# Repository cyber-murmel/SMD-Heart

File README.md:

# SMD Heart
This PCB is supposed the be a pendant for a necklace or similar.
The circuit is a simple 13 stage ring oscillator which makes 13 LEDs fade.
It's powered by a single CR2032 coin cell.

The files are created using KiCAD Version 5.0.0-rc2.
Thus I had to include some footprints and 3D files in this project.

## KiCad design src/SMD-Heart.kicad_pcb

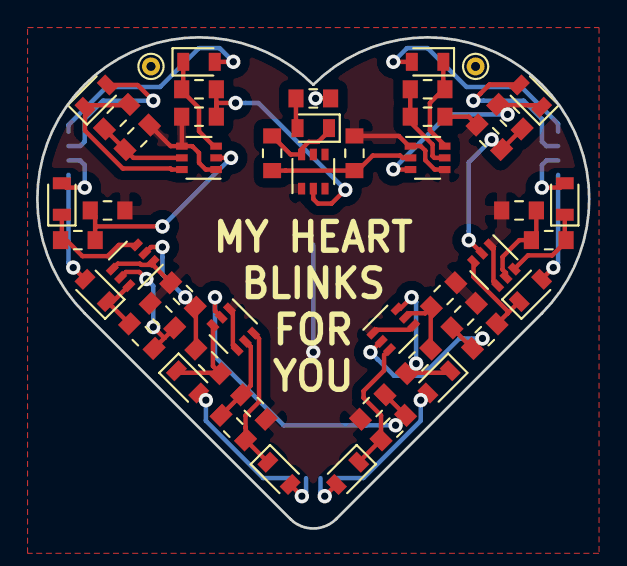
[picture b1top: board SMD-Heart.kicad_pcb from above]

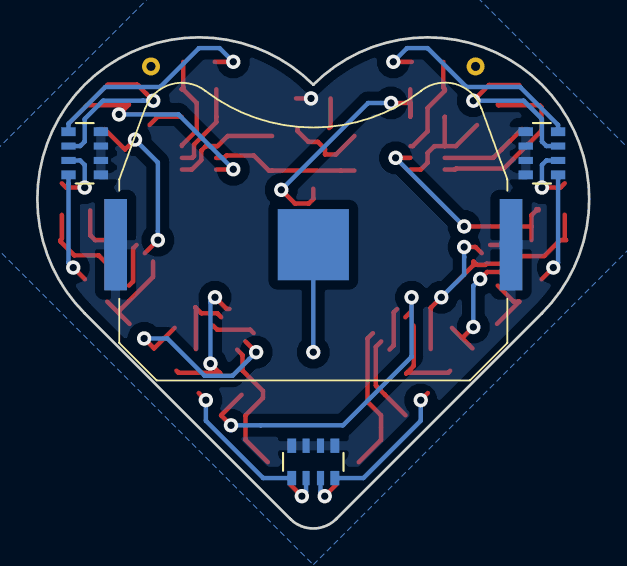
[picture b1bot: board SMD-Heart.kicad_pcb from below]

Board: 2 copper layers, 30.7 x 27.3 mm, 51 parts (4 on the bottom side), 41 nets.

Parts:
BT1: Battery_Cell; Keystone_3034_1x20mm-CoinCell
C1, C2, C3, C4, C5, C6, C7, C8, C9, C10, C11, C12, C13: C; C_0603_1608Metric_Pad0.84x1.00mm_HandSolder
D1, D2, D3, D4, D5, D6, D7, D8, D9, D10, D11, D12, D13: LED; LED_0603_1608Metric_Pad0.67x1.00mm_HandSolder
Q1, Q2, Q3, Q4, Q5, Q6, Q7: FDG1024NZ; SOT-363_SC-70-6
R1, R2, R3, R4, R5, R6, R7, R8, R9, R10, R11, R12, R13: 1meg; R_0603_1608Metric_Pad0.84x1.00mm_HandSolder
R14: R; R_0603_1608Metric_Pad0.84x1.00mm_HandSolder
RN1, RN2, RN3: R_Pack04; R_Array_Convex_4x0603

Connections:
GND: BT1.2, C1.2, C2.2, C3.2, C4.2, C5.2, C6.2, C7.2, C8.2, C9.2, C10.2, C11.2, C12.2, C13.2, Q1.1, Q1.4, Q2.1, Q2.4, Q3.1, Q3.4, Q4.1, Q4.4, Q5.1, Q5.4, Q6.1, Q6.4, Q7.1
unnamed: C1.1, Q1.5, R1.1
unnamed: C2.1, Q2.2, R2.1
unnamed: C3.1, Q2.5, R3.1
unnamed: C4.1, Q3.2, R4.1
unnamed: C5.1, Q3.5, R5.1
unnamed: C6.1, Q4.2, R6.1
unnamed: C7.1, Q4.5, R7.1
unnamed: C8.1, Q5.2, R8.1
unnamed: C9.1, Q5.5, R9.1
unnamed: C10.1, Q6.2, R10.1
unnamed: C11.1, Q6.5, R11.1
unnamed: C12.1, Q7.2, R12.1
unnamed: C13.1, Q1.2, R13.2
unnamed: D1.1, Q1.6, R1.2
unnamed: D1.2, RN1.1
unnamed: D2.1, Q1.3, R2.2
unnamed: D2.2, RN1.2
unnamed: D3.1, Q2.6, R3.2
unnamed: D3.2, RN1.3
unnamed: D4.1, Q2.3, R4.2
unnamed: D4.2, RN1.4
unnamed: D5.1, Q3.6, R5.2
unnamed: D5.2, RN2.1
unnamed: D6.1, Q3.3, R6.2
unnamed: D6.2, RN2.2
unnamed: D7.1, Q4.6, R7.2
unnamed: D7.2, RN2.3
unnamed: D8.1, Q4.3, R8.2
unnamed: D8.2, RN2.4
unnamed: D9.1, Q5.6, R9.2
unnamed: D9.2, RN3.1
unnamed: D10.1, Q5.3, R10.2
unnamed: D10.2, RN3.2
unnamed: D11.1, Q6.6, R11.2
unnamed: D11.2, RN3.3
unnamed: D12.1, Q6.3, R12.2
unnamed: D12.2, RN3.4
unnamed: D13.1, Q7.6, R13.1
unnamed: D13.2, R14.1
VCC: BT1.1, R14.2, RN1.5, RN1.6, RN1.7, RN1.8, RN2.5, RN2.6, RN2.7, RN2.8, RN3.5, RN3.6, RN3.7, RN3.8

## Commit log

2018-03-08 added schematic, PCB, 3D files
2018-03-08 added readme
2018-03-08 added 3D renderings of front and back
2018-03-08 added picture links to readme
2018-03-08 plotted schematic
2018-03-08 png schematic
2018-03-08 acced schematic to readme
2018-03-08 modified 3D stuff
2018-03-08 added gerber export
